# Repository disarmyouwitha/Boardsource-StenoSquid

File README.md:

# StenoSquid-PCB
https://github.com/disarmyouwitha/StenoSquid (Custom ZMK firmware)

Steno Squid adds 16 MB of QSPI flash for Javelin stenography to the left half of the Boardsource Wireless Corne SMT. It is an independent community accessory designed to sit flush on top of the Choc switch plate.

[KiCad project](pcb/steno-squid.kicad_pro) · [Actual-size fit template](pcb/previews/plate-fit-1to1.svg) · [STEP model](pcb/steno-squid.step) · [BOM](pcb/BOM.csv)

## Hardware

- The 22.9 × 46.32 mm board is 1.0 mm thick. The stepped outline clears the estimated USB-C notch, and the components and Pop silkscreen face up.
- Eight bare soldered pins pass through the plate slot into the host PCB. Viewed from above with USB-C at the top, the contact row is at the bottom and pin 1 is on the left. The 2.54 mm pitch and 2.20 mm pin-1 offset from the slot’s left end are provisional.
- The W25Q128JVPIQ WSON flash, 100 nF decoupling capacitor C1 and 10 kΩ CS pull-up R1 are fitted. The optional bulk capacitor C2 and bleed resistor R2 start unpopulated. The breadboard rail test determines whether either is needed.
- The 0.40 mm supply path from the header through C1 to the flash stays on the top copper layer. Ground pours on both layers cover the flash circuit and contact row. The artwork area is copper-free on both layers.

## Host interface

| Contact | Host GPIO or rail | Flash signal | Flash pad |
|---|---|---|---|
| 1 | P0.07 | CS# | 1 |
| 2 | P0.21 | IO0 | 5 |
| 3 | P0.12 | IO3 | 7 |
| 4 | P0.23 | IO1 | 2 |
| 5 | VCC switched by P0.31 | VCC | 8 |
| 6 | GND | GND | 4 |
| 7 | P0.19 | CLK | 6 |
| 8 | P0.05 | IO2 | 3 |

Use this map for the Adafruit flash breakout proof of concept. The left expansion header serves QSPI. The right half can retain its display. The Boardsource firmware branch `steno-squid/locked-pin-map` builds the Studio-enabled left, logging left, right, and both flash probe targets in CI, and it carries the current `main` firmware: the start-up retry, three-image upload and logging diagnostics. Runtime testing is pending. [Boardsource host documentation](https://boardsource.xyz/blogs/guides/wireless-smt-corne-docs) · [Firmware CI for that branch](https://github.com/disarmyouwitha/StenoSquid/actions/workflows/build.yml?query=branch%3Asteno-squid%2Flocked-pin-map)

## Prototype status

KiCad reports zero ERC, DRC, unconnected items and schematic-parity issues with every ERC and DRC category enabled. Physical fit, power and Bluetooth performance still need verification. [CAD validation](pcb/validation.json)

1. Print the fit template at 100% and check its 50 mm scale bar. Confirm the contact row and pin-1 position, USB plug and keycap clearance, plate material and mounting stack before choosing pin length.
2. Check the switched rail on USB and battery. Measure voltage under load, control polarity, shared loads and discharge with the breakout before deciding whether to populate R2 or C2.
3. Identify the host antenna and check its specified clearance against the plate, pins and daughterboard. Compare host and split Bluetooth performance with the module fitted and removed under the same conditions.
4. Review the WSON land pattern and stencil with the assembler. On the prototype, confirm flash ID, quad mode, readback and dictionary integrity across power cycles.

[Pre-order checklist](docs/pre-order-checklist.md) · [Mounting and CAD notes](pcb/README.md) · [Electrical and RF review](docs/design-review.md) · [Source credits and license status](ATTRIBUTION.md) · [Design history](docs/history.md)

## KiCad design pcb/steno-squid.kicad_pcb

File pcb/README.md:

# Plate-mounted Steno Squid

[KiCad project](steno-squid.kicad_pro) · [Front](previews/front-pop.png) · [Back](previews/back.png) · [1:1 fit template](previews/plate-fit-1to1.svg) · [STEP](steno-squid.step) · [BOM](BOM.csv) · [Validation](validation.json)

The 22.9 × 46.32 mm, 1.0 mm PCB uses the full-ear outline with a stepped USB-C notch and 1 mm corner radii. It sits on the Choc switch plate with the flash, passives and Pop silkscreen on top. Viewed from above with the USB-C at the top, the contact row is at the bottom and pin 1 is at the left. The underside is solder-masked except at the contact holes. The mounting concept uses eight bare soldered pins through the plate slot. The model represents the board and its populated SMT parts. The local WSON model has a 3.4 × 4.3 mm exposed pad matching the land pattern.

U1, C1 and R1 are fitted. C2 and R2 remain unpopulated until the breadboard rail test. The 0.40 mm supply route from J1 to C1 to U1 stays on the front without vias, and four stitching vias connect the local ground pours. The artwork area has a copper keepout on both layers. The ground pours extend through the contact row to provide a return path for CLK and IO2. A local antenna cutback is an option if Bluetooth testing shows a problem. The antenna location, required clearance and Bluetooth performance remain unverified. [Electrical and RF review](../docs/design-review.md)

KiCad 10.0.7 reports zero ERC, DRC, unconnected items and schematic-parity issues with every ERC and DRC category enabled. The 2.54 mm contact pitch, 2.20 mm pin-1 offset and plate envelope still need physical confirmation.

Print the fit template at actual size and verify its 50 mm bar and 10 mm square. Align the contact row to the slot, then check the USB plug clearance, keycap overhang and plate support. The template comes from the rounded KiCad outline and J1 pad coordinates. After measuring, update J1 and its routing if needed, synchronize the pin-1 offset in `interface.json`, and regenerate the template with `python3 tools/make_fit_template.py`. Measure the plate and host stack before choosing the pin length. Confirm the switched rail on USB and battery and measure its fall time with the breadboard flash.

[Plate geometry and provisional antenna assumptions](../docs/plate-geometry.md)

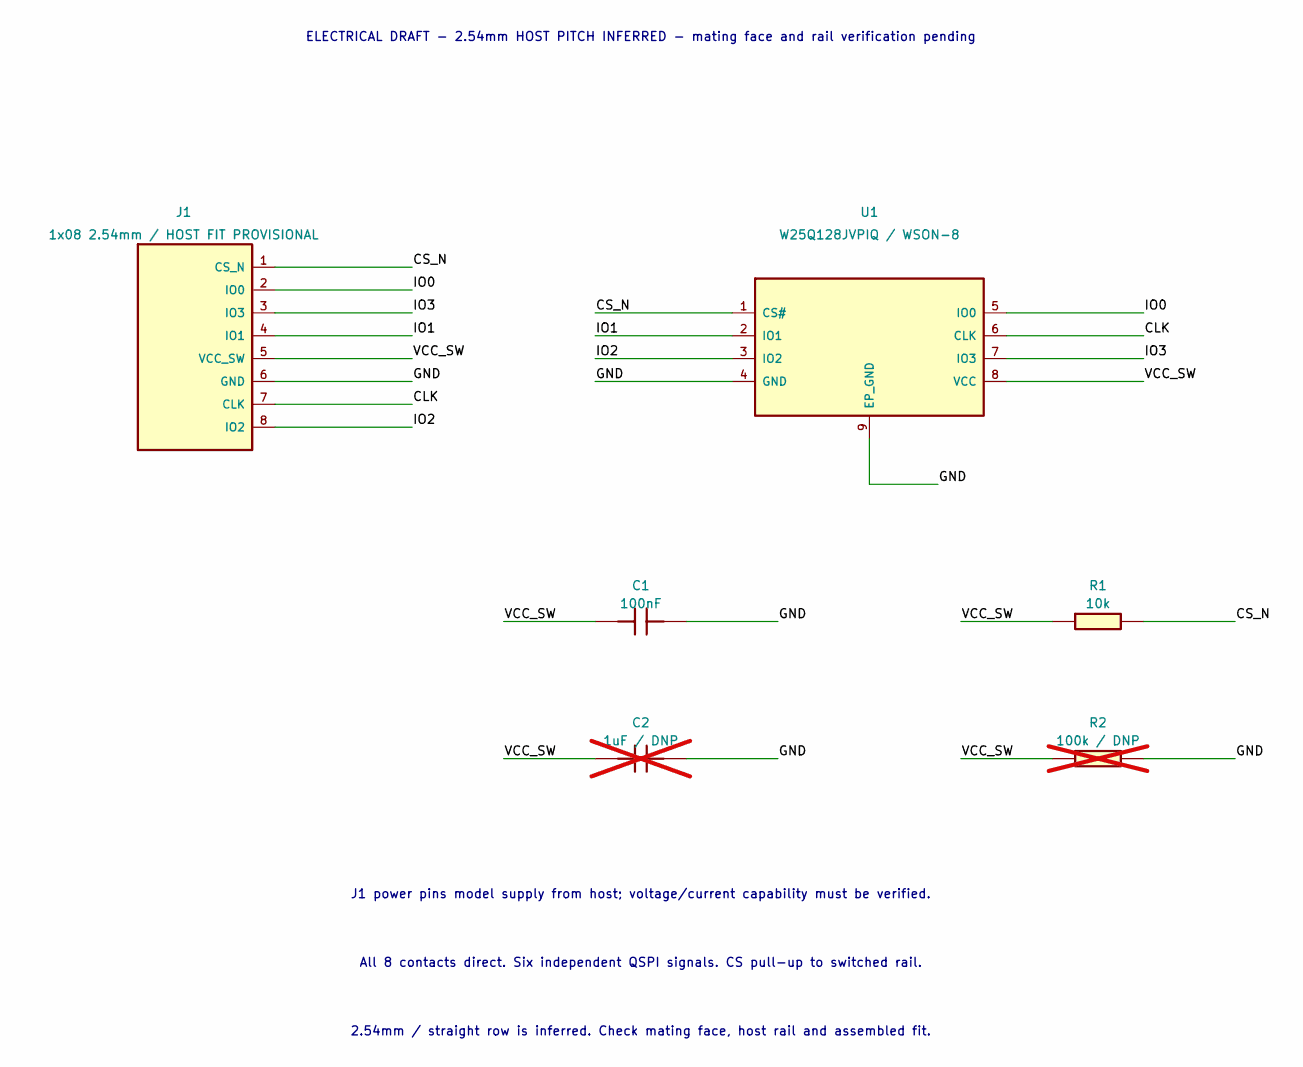
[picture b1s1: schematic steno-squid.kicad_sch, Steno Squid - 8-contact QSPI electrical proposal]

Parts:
C1: 100nF; C_0603_1608Metric
C2: 1uF / DNP; C_0603_1608Metric; not fitted
J1: 1x08 2.54mm / HOST FIT PROVISIONAL; PinHeader_1x08_P2.54mm_Vertical
R1: 10k; R_0603_1608Metric
R2: 100k / DNP; R_0603_1608Metric; not fitted
U1: W25Q128JVPIQ / WSON-8; WSON-8_6x5mm_P1.27mm_EP3.4x4.3mm

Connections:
/CLK: J1.7 (CLK), U1.6 (CLK)
/CS_N: J1.1 (CS_N), R1.2, U1.1 (CS#)
/GND: C1.2, C2.2, J1.6 (GND), R2.2, U1.4 (GND), U1.9 (EP_GND)
/IO0: J1.2 (IO0), U1.5 (IO0)
/IO1: J1.4 (IO1), U1.2 (IO1)
/IO2: J1.8 (IO2), U1.3 (IO2)
/IO3: J1.3 (IO3), U1.7 (IO3)
/VCC_SW: C1.1, C2.1, J1.5 (VCC_SW), R1.1, R2.1, U1.8 (VCC)

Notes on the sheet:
ELECTRICAL DRAFT - 2.54mm HOST PITCH INFERRED - mating face and rail verification pending
J1 power pins model supply from host; voltage/current capability must be verified.
All 8 contacts direct. Six independent QSPI signals. CS pull-up to switched rail.
2.54mm / straight row is inferred. Check mating face, host rail and assembled fit.

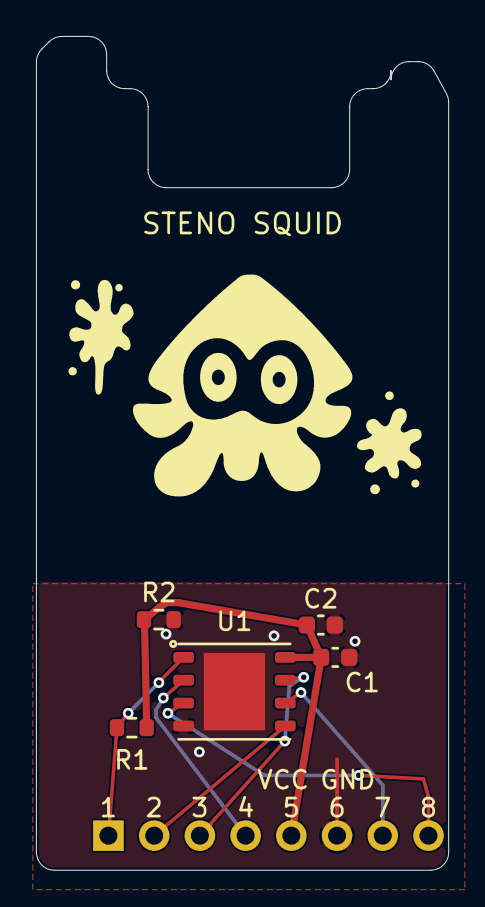
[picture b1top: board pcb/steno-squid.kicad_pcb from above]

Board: 2 copper layers, 22.9 x 46.3 mm, 6 parts (0 on the bottom side), 8 nets.

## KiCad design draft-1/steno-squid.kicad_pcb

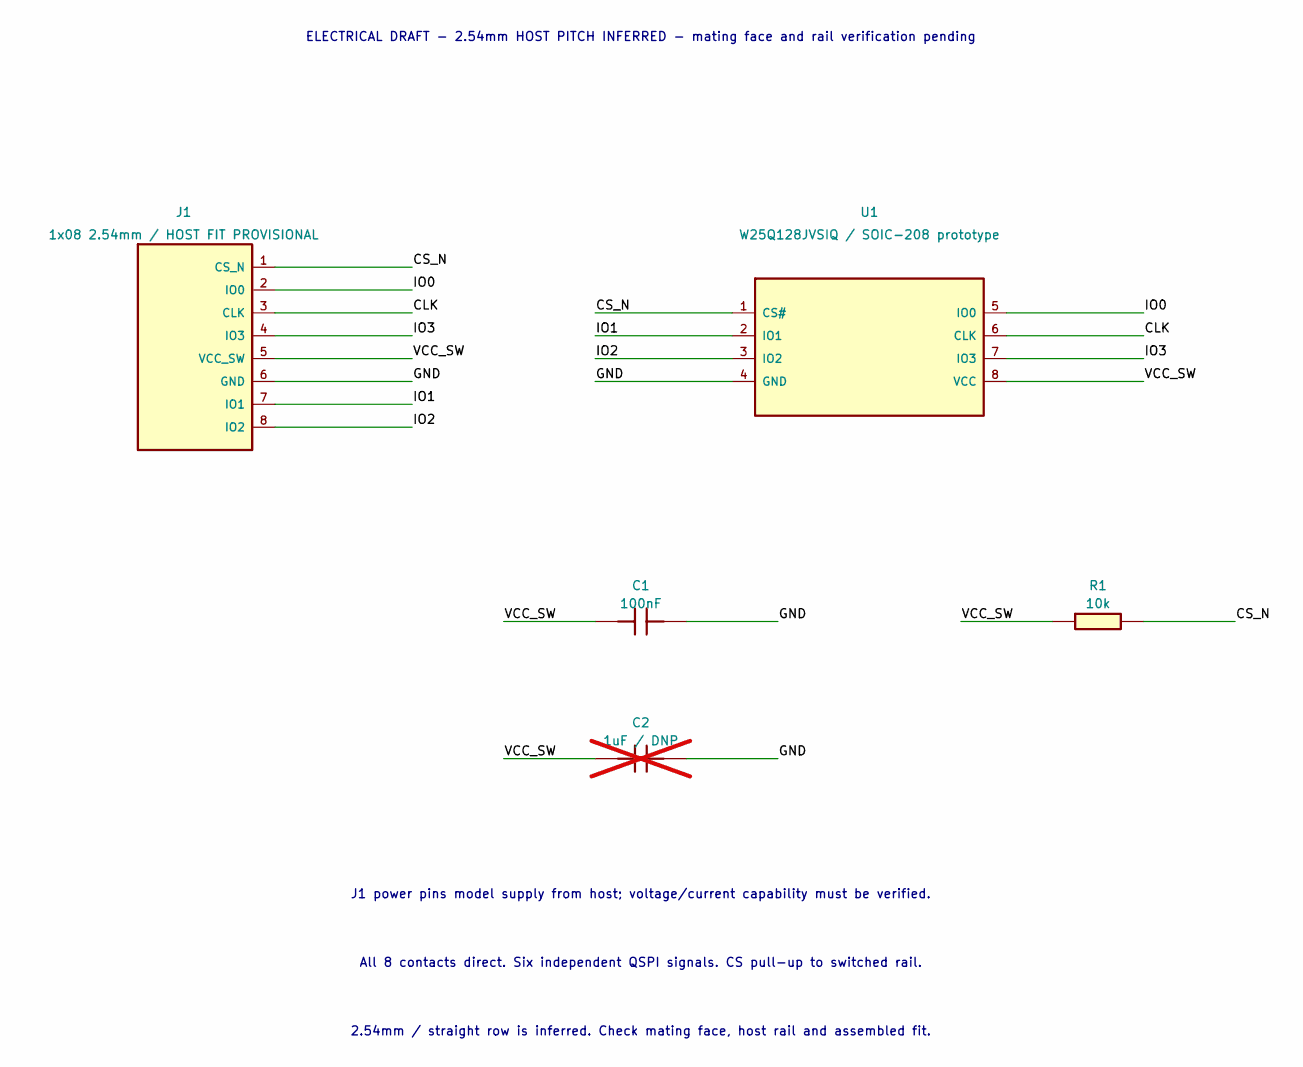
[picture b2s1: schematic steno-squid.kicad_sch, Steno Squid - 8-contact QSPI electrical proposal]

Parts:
C1: 100nF; C_0603_1608Metric
C2: 1uF / DNP; C_0603_1608Metric; not fitted
J1: 1x08 2.54mm / HOST FIT PROVISIONAL; PinHeader_1x08_P2.54mm_Vertical
R1: 10k; R_0603_1608Metric
U1: W25Q128JVSIQ / SOIC-208 prototype; SOIC-8_5.3x5.3mm_P1.27mm

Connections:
/CLK: J1.3 (CLK), U1.6 (CLK)
/CS_N: J1.1 (CS_N), R1.2, U1.1 (CS#)
/GND: C1.2, C2.2, J1.6 (GND), U1.4 (GND)
/IO0: J1.2 (IO0), U1.5 (IO0)
/IO1: J1.7 (IO1), U1.2 (IO1)
/IO2: J1.8 (IO2), U1.3 (IO2)
/IO3: J1.4 (IO3), U1.7 (IO3)
/VCC_SW: C1.1, C2.1, J1.5 (VCC_SW), R1.1, U1.8 (VCC)

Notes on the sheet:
ELECTRICAL DRAFT - 2.54mm HOST PITCH INFERRED - mating face and rail verification pending
J1 power pins model supply from host; voltage/current capability must be verified.
All 8 contacts direct. Six independent QSPI signals. CS pull-up to switched rail.
2.54mm / straight row is inferred. Check mating face, host rail and assembled fit.

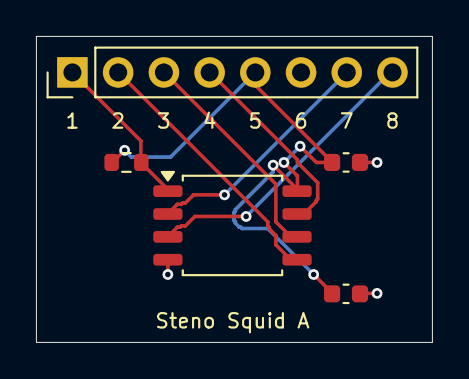
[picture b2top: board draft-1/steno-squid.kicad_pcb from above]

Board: 2 copper layers, 22.0 x 17.0 mm, 5 parts (0 on the bottom side), 8 nets.
